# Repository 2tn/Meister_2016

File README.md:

# Meister_2016
2016年度Meister鳥人間プロジェクトに搭載した飛行ロガー、「われのロガー3」のプログラム及び発注基板データ。

搭載したパーツは
- LPC11U35FHI33 (メインマイコン)
- MPU9250 (9軸センサー)
- MPL3115A2 (気圧センサー)
- NEO-7M (GPS)
- LTC4055 (LiPo充電制御チップ)
- TPS63001DRCT (3.3V DC/DCコンバーター)
- TWE-Lite (各搭載センサーとの通信用)

## われのロガー3
メインマイコンのプログラム。EMとFMのプロジェクトがあるが、FMのほうが最終的な完成版。
## 機速計
機速計のプログラム。よく覚えていない。
## 表示器 (7セグLED)
表示器のプログラム
## 表示器 (Android)
搭載したスマホ表示器のプログラム
## ダウンリンク
機体に積んであるスマホから、携帯回線経由で常時データをサーバーにアップロードしている。

このプログラムはそのデータを地上にいる観客がスマホで見るためのもの
## 基板
発注した基板データ、たくさんある…
- main_16

  われのロガー3の基板データ
- main_16_writer

  われのロガー3専用のデバッグ用機器、われのロガー3の下にはめてUSBでPCと接続することで、われのロガー3をデバッグできる。
  プログラムは、トラ技ARMライターのものをつかう。
- main_15

  2015年度の基板を回路図に落とし込んだもの  
- display

  表示器の回路設計図
- speedmeter

  機速計の回路設計図
- TWE-Lite_USB

  TWE LiteにUSB-UART変換チップをくっつけて、PCで使いやすくするための基板

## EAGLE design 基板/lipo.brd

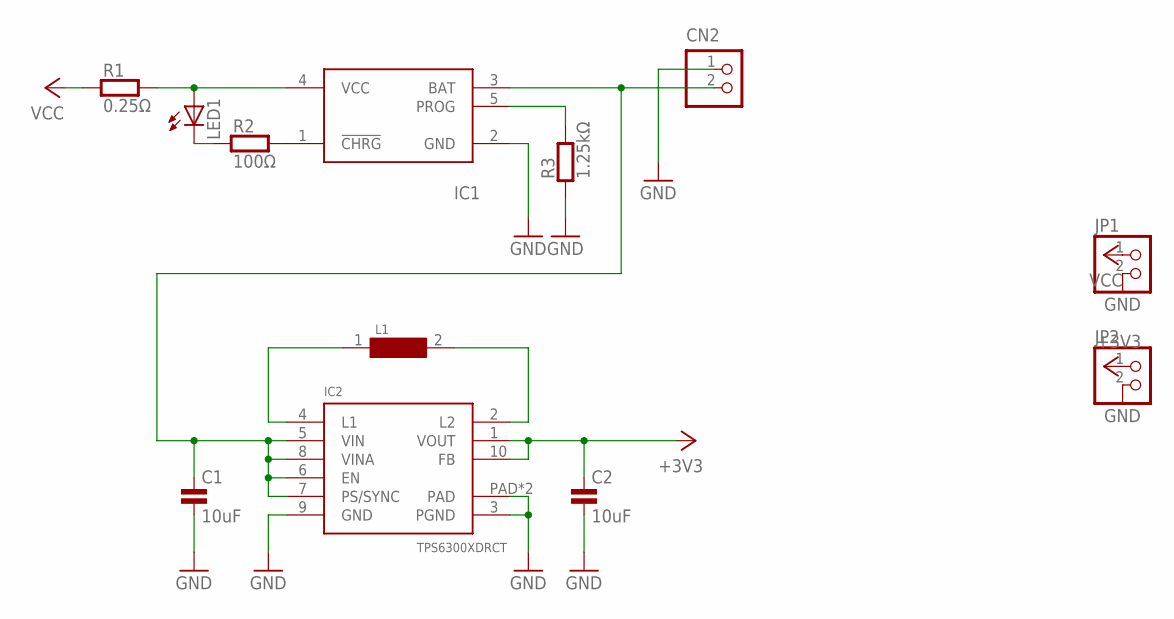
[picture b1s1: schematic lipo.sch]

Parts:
C1, C2: 10uF; 0603
CN2: S2B-PH-K-S
IC1: LTC4054; TSOT23-5
IC2: TPS6300XDRCT; S-PVSON-N10
JP1, JP2: PINHD-1X2; 1X02
L1: VLF4012ST
LED1: LEDSML0603; SML0603
R1: 0.25Ω; 0603
R2: 100Ω; 0603
R3: 1.25kΩ; 0603

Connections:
+3V3: C2.1, IC2.1 (VOUT), IC2.10 (FB), JP2.1
GND: C1.2, C2.2, CN2.1, IC1.2 (GND), IC2.3 (PGND), IC2.9 (GND), IC2.PAD, IC2.PAD@1 (PAD), JP1.2, JP2.2, R3.1
unnamed: IC1.5 (PROG), R3.2
unnamed: IC1.4 (VCC), LED1.A, R1.2
unnamed: IC1.1 (!CHRG!), R2.2
unnamed: LED1.C, R2.1
unnamed: IC2.4 (L1), L1.1
unnamed: IC2.2 (L2), L1.2
unnamed: C1.1, CN2.2, IC1.3 (BAT), IC2.5 (VIN), IC2.6 (EN), IC2.7 (PS/SYNC), IC2.8 (VINA)
VCC: JP1.1, R1.1

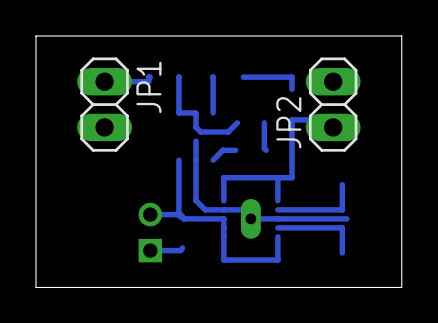
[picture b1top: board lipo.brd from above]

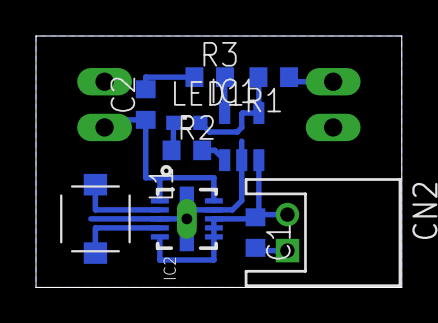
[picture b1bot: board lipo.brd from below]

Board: 2 copper layers, 20.3 x 14.0 mm, 12 parts (10 on the bottom side), 10 nets.

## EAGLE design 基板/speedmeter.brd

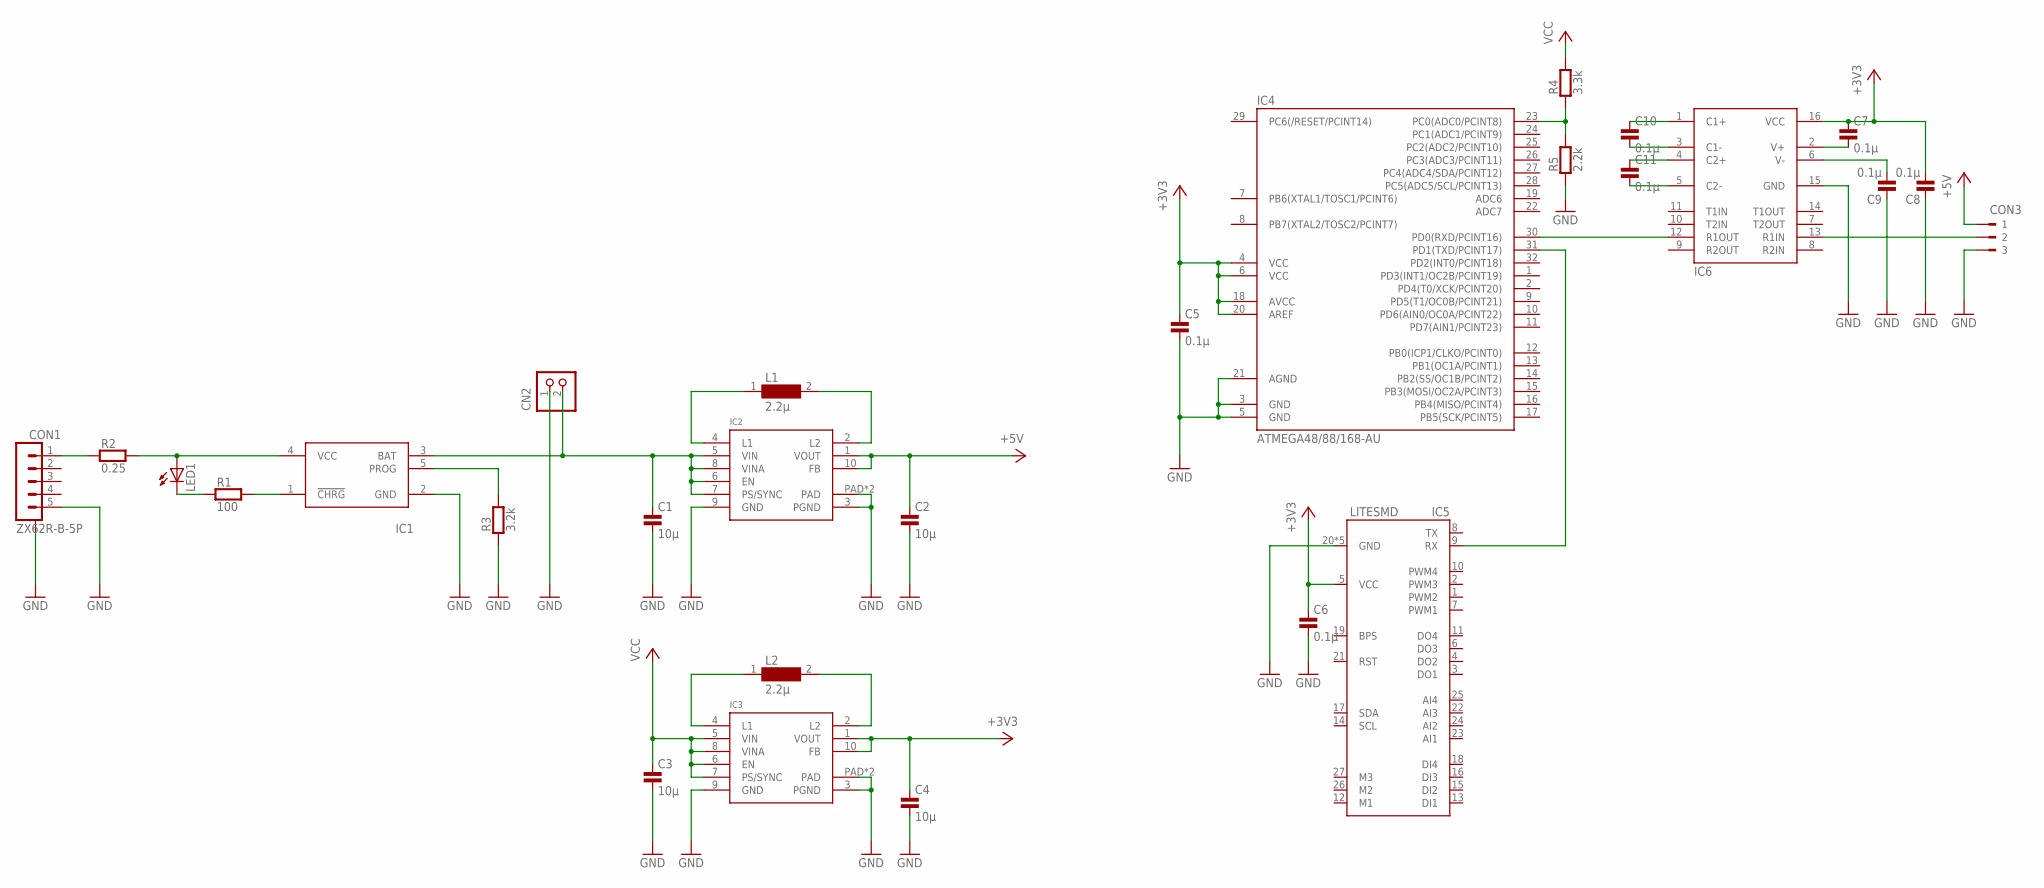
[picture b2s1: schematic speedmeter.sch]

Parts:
C1, C2, C3, C4: 10μ; 0603
C5, C6, C7, C8, C9, C10, C11: 0.1μ; 0603
CN2: S2B-PH-K-S
CON1: ZX62R-B-5P; MICRO-B
CON3: 180-3
IC1: LTC4054; TSOT23-5
IC2, IC3: TPS6300XDRCT; S-PVSON-N10
IC4: ATMEGA48/88/168-AU; TQFP32-08
IC5: LITESMD; LITE
IC6: ADM3202ARN; SOP16
L1, L2: 2.2μ; VLF4012ST
LED1: LEDSML0603; SML0603
R1: 100; 0603
R2: 0.25; 0603
R3: 3.2k; 0603
R4: 3.3k; 0603
R5: 2.2k; 0603

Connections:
+3V3: C4.1, C5.1, C6.1, C7.1, C8.2, IC3.1 (VOUT), IC3.10 (FB), IC4.4 (VCC), IC4.6 (VCC), IC4.18 (AVCC), IC4.20 (AREF), IC5.5 (VCC), IC6.16 (VCC)
+5V: C2.1, CON3.1, IC2.1 (VOUT), IC2.10 (FB)
GND: C1.2, C2.2, C3.2, C4.2, C5.2, C6.2, C8.1, C9.1, CN2.1, CON1.5 (1.VBUS), CON1.CASE@1, CON1.CASE@2, CON1.CASE@3, CON1.CASE@4, CON3.3, IC1.2 (GND), IC2.3 (PGND), IC2.9 (GND), IC2.PAD, IC2.PAD@1 (PAD), IC3.3 (PGND), IC3.9 (GND), IC3.PAD, IC3.PAD@1 (PAD), IC4.3 (GND), IC4.5 (GND), IC4.21 (AGND), IC5.20 (GND), IC5.28 (GND), IC5.30 (GND), IC5.31 (GND), IC5.32 (GND), IC6.15 (GND), R3.1, R5.1
unnamed: CON1.1 (5.GND), R2.1
unnamed: IC1.4 (VCC), LED1.A, R2.2
unnamed: LED1.C, R1.1
unnamed: IC1.1 (!CHRG!), R1.2
unnamed: IC1.5 (PROG), R3.2
unnamed: IC2.4 (L1), L1.1
unnamed: IC2.2 (L2), L1.2
unnamed: CON3.2, IC6.13 (R1IN)
unnamed: IC3.4 (L1), L2.1
unnamed: IC3.2 (L2), L2.2
unnamed: IC4.23 (PC0(ADC0/PCINT8)), R4.1, R5.2
unnamed: IC4.31 (PD1(TXD/PCINT17)), IC5.9 (RX)
unnamed: C7.2, IC6.2 (V+)
unnamed: C9.2, IC6.6 (V-)
unnamed: C10.1, IC6.1 (C1+)
unnamed: C10.2, IC6.3 (C1-)
unnamed: C11.1, IC6.4 (C2+)
unnamed: C11.2, IC6.5 (C2-)
unnamed: IC4.30 (PD0(RXD/PCINT16)), IC6.12 (R1OUT)
VCC: C1.1, C3.1, CN2.2, IC1.3 (BAT), IC2.5 (VIN), IC2.6 (EN), IC2.7 (PS/SYNC), IC2.8 (VINA), IC3.5 (VIN), IC3.6 (EN), IC3.7 (PS/SYNC), IC3.8 (VINA), R4.2

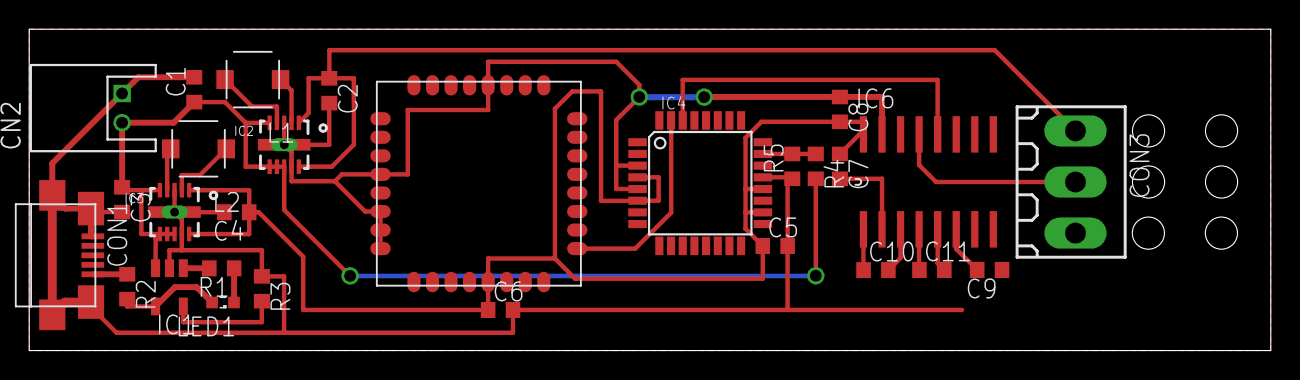
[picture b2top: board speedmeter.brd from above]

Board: 2 copper layers, 85.0 x 22.0 mm, 28 parts (0 on the bottom side), 23 nets.

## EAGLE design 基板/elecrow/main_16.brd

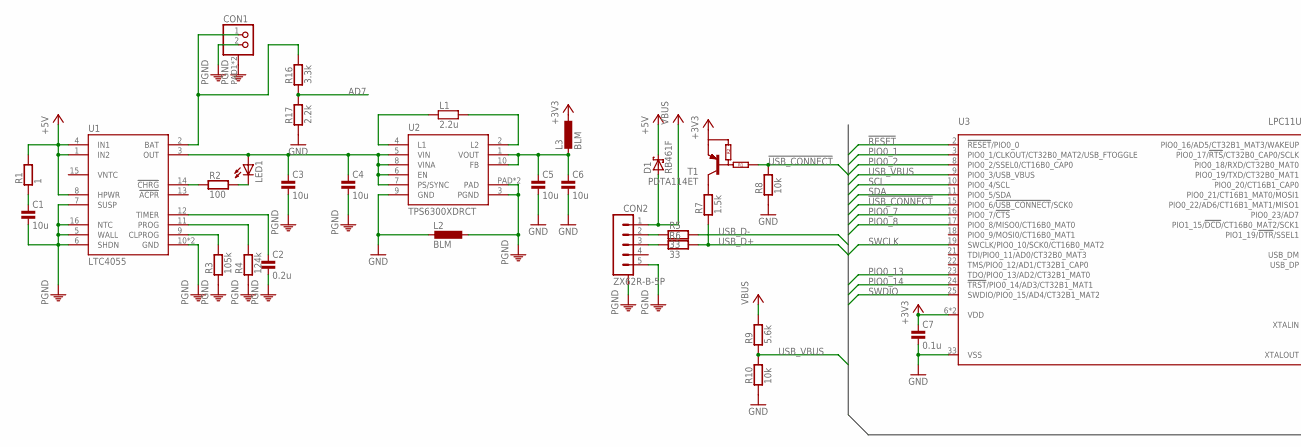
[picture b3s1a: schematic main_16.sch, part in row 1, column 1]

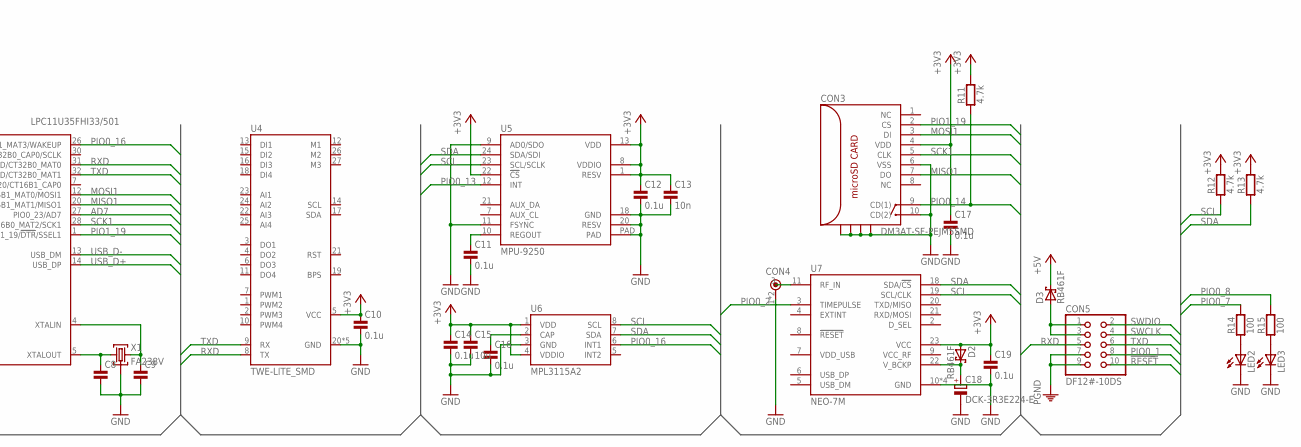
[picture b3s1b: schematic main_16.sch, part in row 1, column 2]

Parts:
C1, C3, C4, C5, C6: 10u; 0603
C2: 0.2u; 0402
C7, C10, C11, C12, C14, C16, C17, C19: 0.1u; 0402
C8, C9: C0402; 0402
C13: 10n; 0402
C15: 10u; 0402
C18: DCK-3R3E224-E
CON1: JST-PH2
CON2: ZX62R-B-5P; MICRO-B
CON3: DM3AT-SF-PEJM5SMD; DM3AT-SF-PEJM5
CON4: U.FL; U.FL-R-SMT-1
CON5: DF12#-10DS; DF12A-10DS
D1, D2, D3: RB461F; UMD3
L1: 2.2u; VLF4012ST
L2, L3: BLM; C0603K
LED1, LED2, LED3: LEDSML0603; SML0603
R1: 1; 0402
R2, R14, R15: 100; 0402
R3: 105k; 0402
R4: 124k; 0402
R5, R6: 33; 0402
R7: 1.5k; 0402
R8, R10: 10k; 0402
R9: 5.6k; 0402
R11, R12, R13: 4.7k; 0402
R16: 3.3k; 0402
R17: 2.2k; 0402
T1: PDTA114ET; SOT23
U1: LTC4055; QFN16
U2: TPS6300XDRCT; S-PVSON-N10
U3: LPC11U35FHI33/501; SOT617-3
U4: TWE-LITE_SMD; LITE
U5: MPU-9250
U6: MPL3115A2
U7: NEO-7M
X1: FA238V; V66RA

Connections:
!RESET!: CON5.10, U3.2 (!RESET!/PIO0_0)
!USB_CONNECT!: R8.2, T1.1 (INPUT), U3.15 (PIO0_6/!USB_CONNECT!/SCK0)
+3V3: C7.1, C10.1, C12.1, C13.1, C14.1, C15.1, C17.1, C19.1, CON3.4 (VDD), D2.2 (A), L3.1, R11.2, R12.2, R13.2, T1.2 (E), U3.6 (VDD), U3.29 (VDD), U4.5 (VCC), U5.1 (RESV), U5.8 (VDDIO), U5.13 (VDD), U5.22 (!CS!), U6.1 (VDD), U6.4 (VDDIO), U7.23 (VCC)
+5V: D1.3 (C), D3.3 (C), R1.2, U1.1 (IN2), U1.4 (IN1), U1.8 (HPWR)
AD7: R16.1, R17.2, U3.27 (PIO0_23/AD7)
GND: C5.2, C6.2, C7.2, C8.2, C9.2, C10.2, C11.2, C12.2, C13.2, C14.2, C15.2, C16.2, C17.2, C18.1 (-), C19.2, CON3.6 (VSS), CON3.10 (CD(2)), CON3.P$10, CON3.P$11, CON3.P$12, CON3.P$14, CON4.1 (GND), CON4.2 (GND), L2.2, LED2.C, LED3.C, R8.1, R10.1, R17.1, U2.9 (GND), U3.33 (VSS), U4.20 (GND), U4.28 (GND), U4.30 (GND), U4.31 (GND), U4.32 (GND), U5.9 (AD0/SDO), U5.11 (FSYNC), U5.18 (GND), U5.20 (RESV), U5.PAD, U6.3 (GND), U7.10 (GND), U7.12 (GND), U7.13 (GND), U7.24 (GND), X1.P2GND (GND), X1.P4GND (GND)
MISO1: CON3.7 (DO), U3.20 (PIO0_22/AD6/CT16B1_MAT1/MISO1)
MOSI1: CON3.3 (DI), U3.12 (PIO0_21/CT16B1_MAT0/MOSI1)
unnamed: C8.1, U3.5 (XTALOUT), X1.P1X1 (X1)
unnamed: CON2.2 (2.D-), R5.1
unnamed: C9.1, U3.4 (XTALIN), X1.P3X2 (X2)
unnamed: CON2.3 (3.D+), R6.1
unnamed: R7.2, T1.3 (C)
unnamed: LED3.A, R15.1
unnamed: CON4.3 (RF), U7.11 (RF_IN)
unnamed: C16.1, U6.2 (CAP)
unnamed: L1.2, U2.2 (L2)
unnamed: C11.1, U5.10 (REGOUT)
unnamed: L1.1, U2.4 (L1)
unnamed: LED2.A, R14.1
unnamed: C1.1, R1.1
unnamed: C5.1, C6.1, L3.2, U2.1 (VOUT), U2.10 (FB)
unnamed: CON5.1, CON5.3, D3.2 (A)
unnamed: R3.2, U1.9 (CLPROG)
unnamed: R4.2, U1.11 (PROG)
unnamed: C2.1, U1.12 (TIMER)
unnamed: R2.1, U1.14 (!CHRG!)
unnamed: LED1.C, R2.2
unnamed: C3.1, C4.1, LED1.A, U1.3 (OUT), U2.5 (VIN), U2.6 (EN), U2.7 (PS/SYNC), U2.8 (VINA)
unnamed: CON1.1, R16.2, U1.2 (BAT)
unnamed: C18.2 (+), D2.3 (C), U7.22 (V_BCKP)
PGND: C1.2, C2.2, C3.2, C4.2, CON1.2, CON1.PAD1, CON1.PAD2, CON2.5 (5.GND), CON2.CASE@1, CON2.CASE@2, CON2.CASE@3, CON2.CASE@4, CON5.7, CON5.9, L2.1, R3.1, R4.1, U1.5 (WALL), U1.6 (SHDN), U1.7 (SUSP), U1.10 (GND), U1.16 (NTC), U1.PAD (GND), U2.3 (PGND), U2.PAD, U2.PAD@1 (PAD)
PIO0_1: CON5.8, U3.3 (PIO0_1/CLKOUT/CT32B0_MAT2/USB_FTOGGLE)
PIO0_2: U3.8 (PIO0_2/SSEL0/CT16B0_CAP0), U7.3 (TIMEPULSE)
PIO0_7: R14.2, U3.16 (PIO0_7/!CTS!)
PIO0_8: R15.2, U3.17 (PIO0_8/MISO0/CT16B0_MAT0)
PIO0_13: U3.23 (TDO/PIO0_13/AD2/CT32B1_MAT0), U5.12 (INT)
PIO0_14: CON3.9 (CD(1)), R11.1, U3.24 (!TRST!/PIO0_14/AD3/CT32B1_MAT1)
PIO0_16: U3.26 (PIO0_16/AD5/CT32B1_MAT3/WAKEUP), U6.6 (INT1)
PIO1_19: CON3.2 (CS), U3.1 (PIO1_19/!DTR!/SSEL1)
RXD: CON5.5, U3.31 (PIO0_18/RXD/CT32B0_MAT0), U4.8 (TX)
SCK1: CON3.5 (CLK), U3.28 (PIO1_15/!DCD!/CT16B0_MAT2/SCK1)
SCL: R12.1, U3.10 (PIO0_4/SCL), U5.23 (SCL/SCLK), U6.8 (SCL), U7.19 (SCL/CLK)
SDA: R13.1, U3.11 (PIO0_5/SDA), U5.24 (SDA/SDI), U6.7 (SDA), U7.18 (SDA/!CS!)
SWCLK: CON5.4, U3.19 (SWCLK/PIO0_10/SCK0/CT16B0_MAT2)
SWDIO: CON5.2, U3.25 (SWDIO/PIO0_15/AD4/CT32B1_MAT2)
TXD: CON5.6, U3.32 (PIO0_19/TXD/CT32B0_MAT1), U4.9 (RX)
USB_D+: R6.2, R7.1, U3.14 (USB_DP)
USB_D-: R5.2, U3.13 (USB_DM)
USB_VBUS: R9.1, R10.2, U3.9 (PIO0_3/USB_VBUS)
VBUS: CON2.1 (1.VBUS), D1.2 (A), R9.2
VDD_USB: U7.7 (VDD_USB)
VNTC: U1.15 (VNTC)

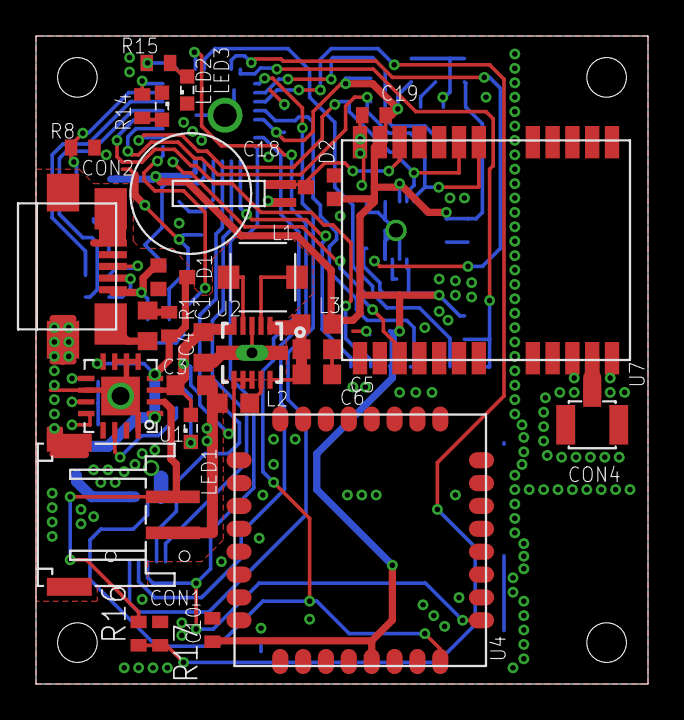
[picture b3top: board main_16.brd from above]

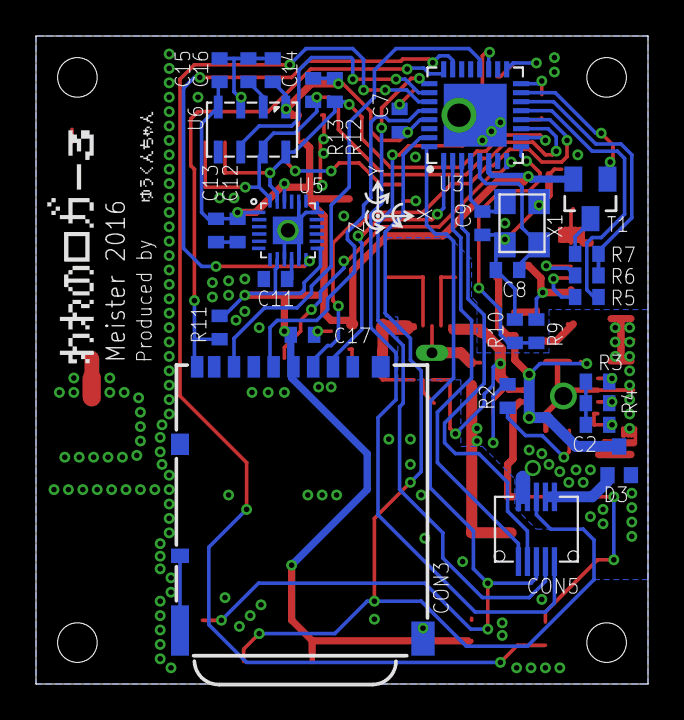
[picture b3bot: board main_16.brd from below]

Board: 2 copper layers, 34.0 x 36.0 mm, 60 parts (31 on the bottom side), 51 nets.

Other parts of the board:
U$1: DIRECTION

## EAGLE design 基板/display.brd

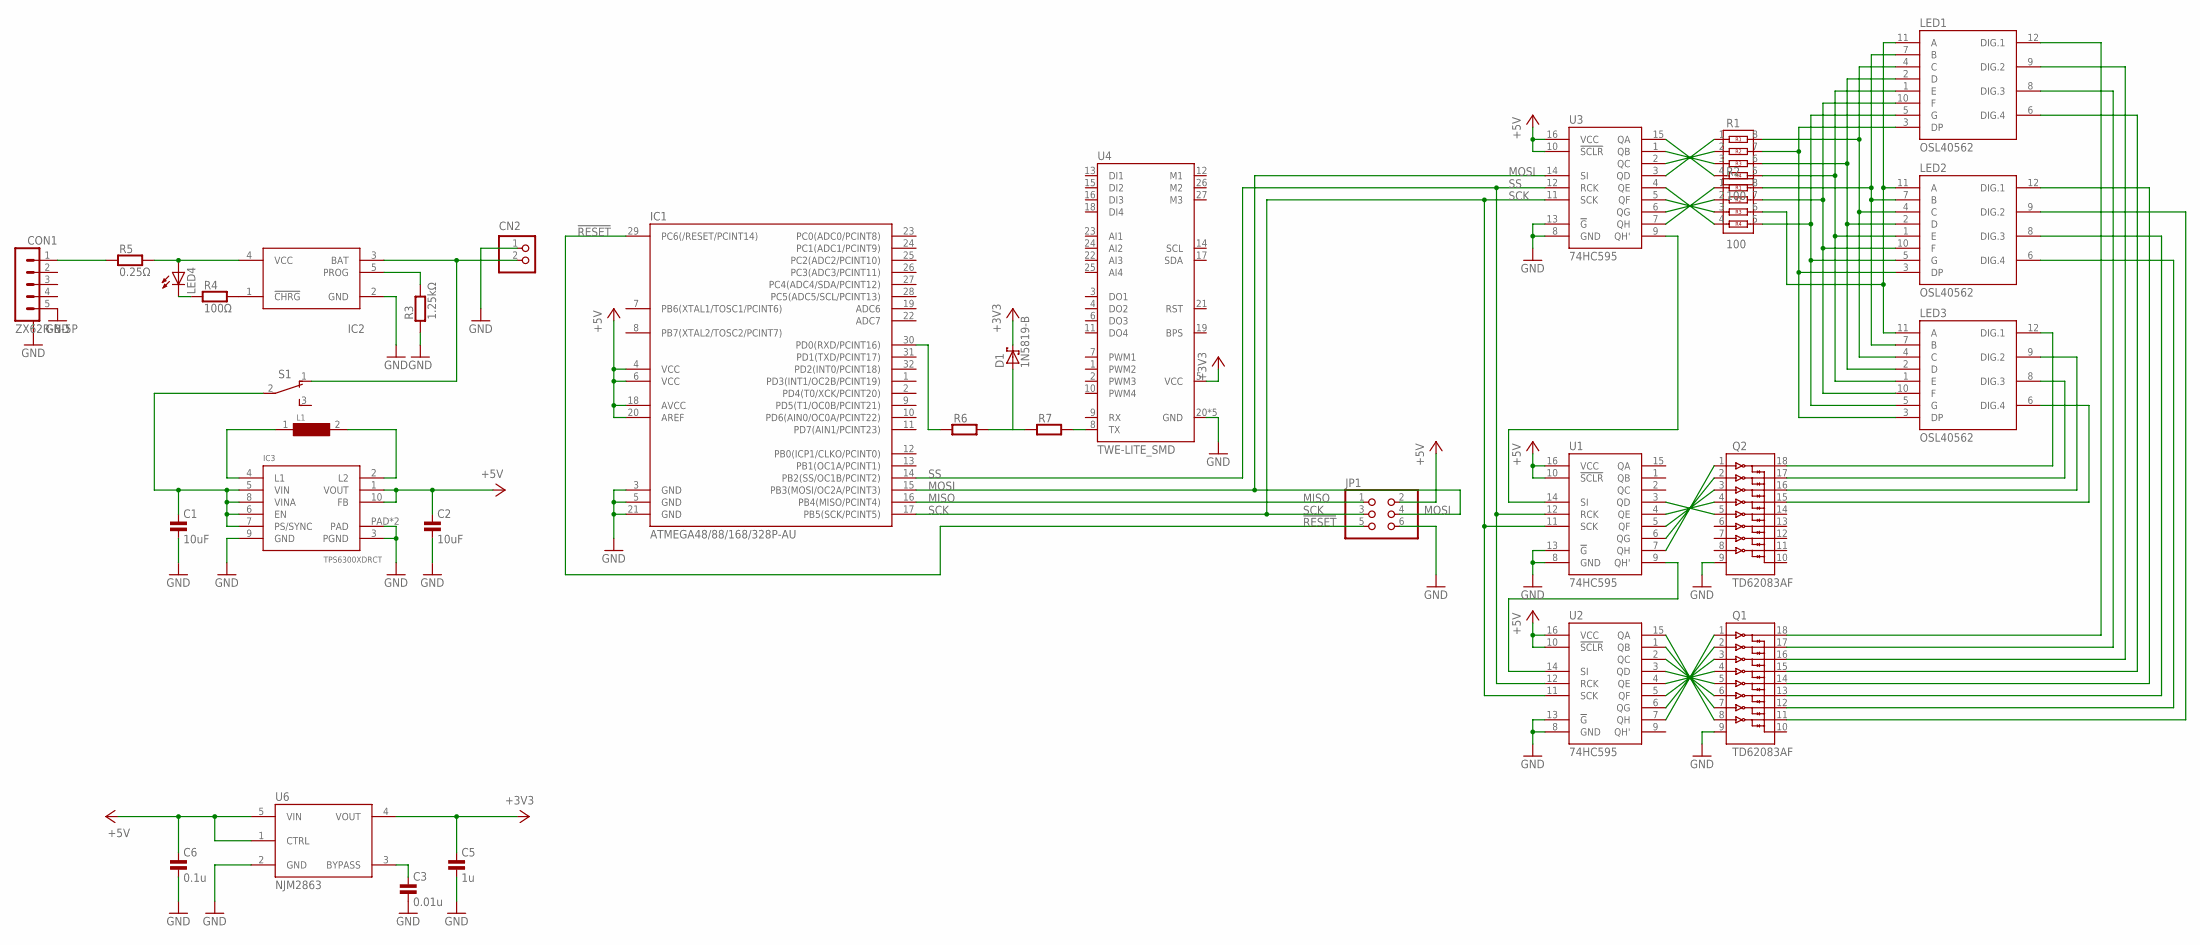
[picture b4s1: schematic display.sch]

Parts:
C1, C2: 10uF; 0603@1
C3: 0.01u; 0603@1
C5: 1u; 0603@1
C6: 0.1u; 0603@1
CN2: S2B-PH-K-S
CON1: ZX62R-B-5P; MICRO-B
D1: 1N5819-B; DO41-7.6
IC1: ATMEGA48/88/168/328P-AU; TQFP32
IC2: LTC4054; TSOT23-5
IC3: TPS6300XDRCT; S-PVSON-N10
JP1: PINHD-2X3; 2X03
L1: VLF4012ST
LED1, LED2, LED3: OSL40562; 7SEG_4DIG
LED4: LEDSML0603; SML0603
Q1, Q2: TD62083AF; SOP18
R1, R2: 100; BCN164AB
R3: 1.25kΩ; 0603
R4: 100Ω; 0603
R5: 0.25Ω; 0603
R6, R7: R0204/5; 0204/5
S1: SS-12D00
U1, U2, U3: 74HC595; SOP16
U4: TWE-LITE_SMD; LITE
U6: NJM2863; SOT23_5PIN

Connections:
!RESET!: IC1.29 (PC6(/RESET/PCINT14)), JP1.5
+3V2: C1.1, IC3.5 (VIN), IC3.6 (EN), IC3.7 (PS/SYNC), IC3.8 (VINA), S1.2
+3V3: C5.1, D1.C, U4.5 (VCC), U6.4 (VOUT)
+5V: C2.1, C6.1, IC1.4 (VCC), IC1.6 (VCC), IC1.18 (AVCC), IC1.20 (AREF), IC3.1 (VOUT), IC3.10 (FB), JP1.2, U1.10 (!SCLR!), U1.16 (VCC), U2.10 (!SCLR!), U2.16 (VCC), U3.10 (!SCLR!), U3.16 (VCC), U6.1 (CTRL), U6.5 (VIN)
GND: C1.2, C2.2, C3.2, C5.2, C6.2, CN2.1, CON1.5 (5.GND), CON1.CASE@1, CON1.CASE@2, CON1.CASE@3, CON1.CASE@4, IC1.3 (GND), IC1.5 (GND), IC1.21 (GND), IC2.2 (GND), IC3.3 (PGND), IC3.9 (GND), IC3.PAD, IC3.PAD@1 (PAD), JP1.6, Q1.9 (GND), Q2.9 (GND), R3.1, U1.8 (GND), U1.13 (!G!), U2.8 (GND), U2.13 (!G!), U3.8 (GND), U3.13 (!G!), U4.20 (GND), U4.28 (GND), U4.30 (GND), U4.31 (GND), U4.32 (GND), U6.2 (GND)
MISO: IC1.16 (PB4(MISO/PCINT4)), JP1.1
MOSI: IC1.15 (PB3(MOSI/OC2A/PCINT3)), JP1.4, U3.14 (SI)
unnamed: LED1.11 (A), LED2.11 (A), LED3.11 (A), R2.6
unnamed: LED1.7 (B), LED2.7 (B), LED3.7 (B), R2.8
unnamed: LED1.4 (C), LED2.4 (C), LED3.4 (C), R1.8
unnamed: LED1.2 (D), LED2.2 (D), LED3.2 (D), R1.6
unnamed: LED1.1 (E), LED2.1 (E), LED3.1 (E), R1.5
unnamed: LED1.10 (F), LED2.10 (F), LED3.10 (F), R2.7
unnamed: LED1.5 (G), LED2.5 (G), LED3.5 (G), R2.5
unnamed: LED1.3 (DP), LED2.3 (DP), LED3.3 (DP), R1.7
unnamed: CN2.2, IC2.3 (BAT), S1.1 (O)
unnamed: C3.1, U6.3 (BYPASS)
unnamed: Q2.5 (I5), U1.3 (QD)
unnamed: Q2.4 (I4), U1.4 (QE)
unnamed: Q2.3 (I3), U1.5 (QF)
unnamed: Q2.2 (I2), U1.6 (QG)
unnamed: Q2.1 (I1), U1.7 (QH)
unnamed: LED2.9 (DIG.2), Q1.11 (O8)
unnamed: LED2.8 (DIG.3), Q1.13 (O6)
unnamed: LED2.6 (DIG.4), Q1.12 (O7)
unnamed: LED2.12 (DIG.1), Q1.14 (O5)
unnamed: LED1.6 (DIG.4), Q1.15 (O4)
unnamed: LED1.12 (DIG.1), Q1.18 (O1)
unnamed: LED1.8 (DIG.3), Q1.17 (O2)
unnamed: LED1.9 (DIG.2), Q1.16 (O3)
unnamed: LED3.12 (DIG.1), Q2.18 (O1)
unnamed: LED3.9 (DIG.2), Q2.16 (O3)
unnamed: LED3.8 (DIG.3), Q2.17 (O2)
unnamed: LED3.6 (DIG.4), Q2.15 (O4)
unnamed: Q1.8 (I8), U2.15 (QA)
unnamed: Q1.7 (I7), U2.1 (QB)
unnamed: Q1.6 (I6), U2.2 (QC)
unnamed: Q1.5 (I5), U2.3 (QD)
unnamed: Q1.4 (I4), U2.4 (QE)
unnamed: Q1.3 (I3), U2.5 (QF)
unnamed: Q1.2 (I2), U2.6 (QG)
unnamed: Q1.1 (I1), U2.7 (QH)
unnamed: U1.9 (QH'), U2.14 (SI)
unnamed: R1.4, U3.15 (QA)
unnamed: R1.3, U3.1 (QB)
unnamed: R1.2, U3.2 (QC)
unnamed: R1.1, U3.3 (QD)
unnamed: R2.4, U3.4 (QE)
unnamed: R2.3, U3.5 (QF)
unnamed: R2.2, U3.6 (QG)
unnamed: R2.1, U3.7 (QH)
unnamed: U1.14 (SI), U3.9 (QH')
unnamed: IC1.30 (PD0(RXD/PCINT16)), R6.1
unnamed: IC2.5 (PROG), R3.2
unnamed: IC2.4 (VCC), LED4.A, R5.2
unnamed: IC2.1 (!CHRG!), R4.2
unnamed: LED4.C, R4.1
unnamed: IC3.4 (L1), L1.1
unnamed: IC3.2 (L2), L1.2
unnamed: D1.A, R6.2, R7.1
unnamed: R7.2, U4.8 (TX)
unnamed: CON1.1 (1.VBUS), R5.1
SCK: IC1.17 (PB5(SCK/PCINT5)), JP1.3, U1.11 (SCK), U2.11 (SCK), U3.11 (SCK)
SS: IC1.14 (PB2(SS/OC1B/PCINT2)), U1.12 (RCK), U2.12 (RCK), U3.12 (RCK)

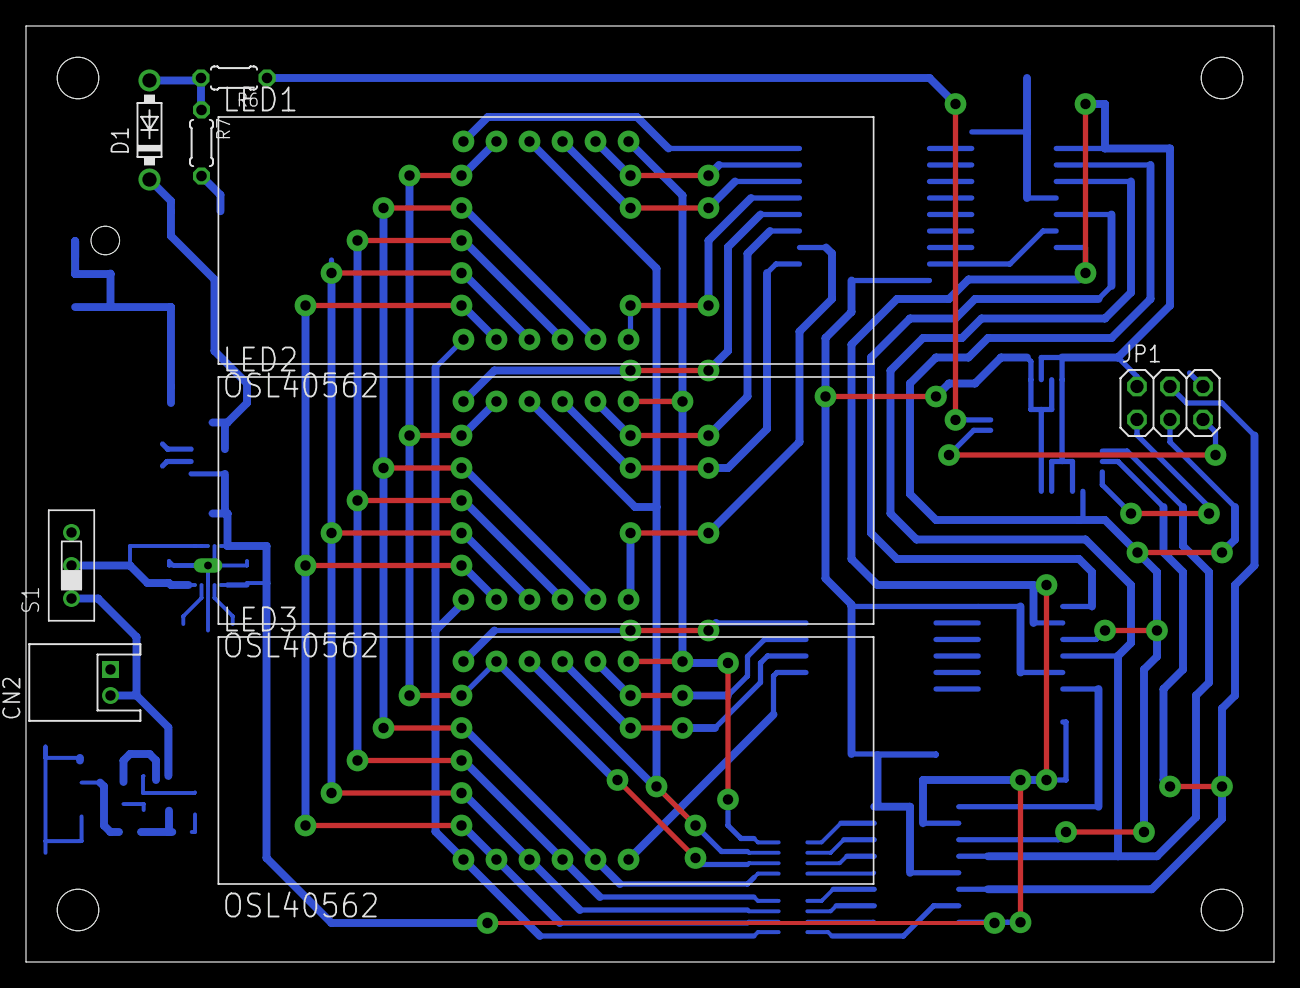
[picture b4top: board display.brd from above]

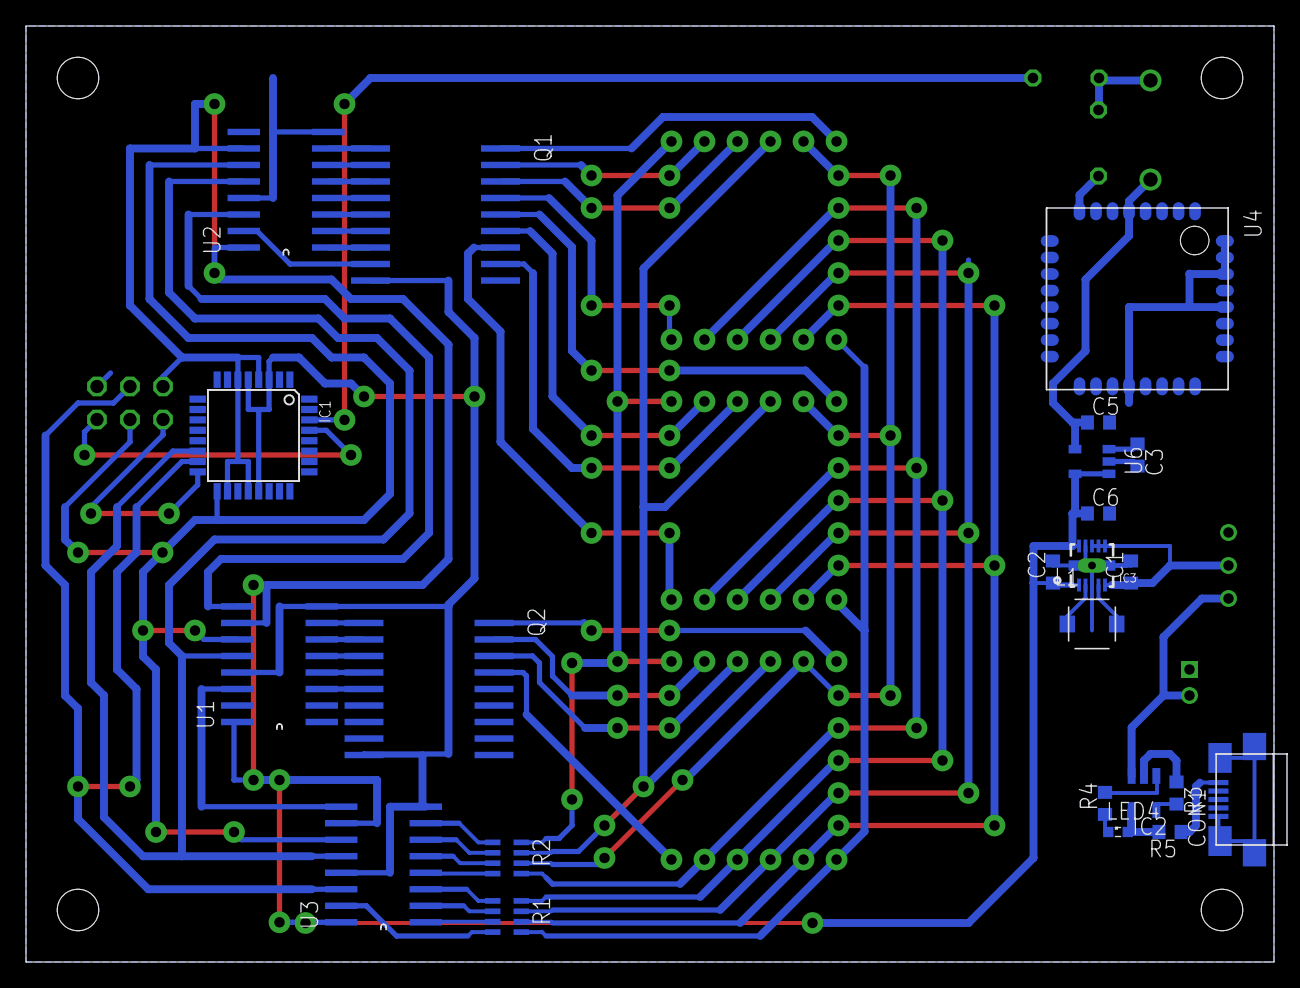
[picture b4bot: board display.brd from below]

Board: 2 copper layers, 96.0 x 72.0 mm, 32 parts (23 on the bottom side), 64 nets.

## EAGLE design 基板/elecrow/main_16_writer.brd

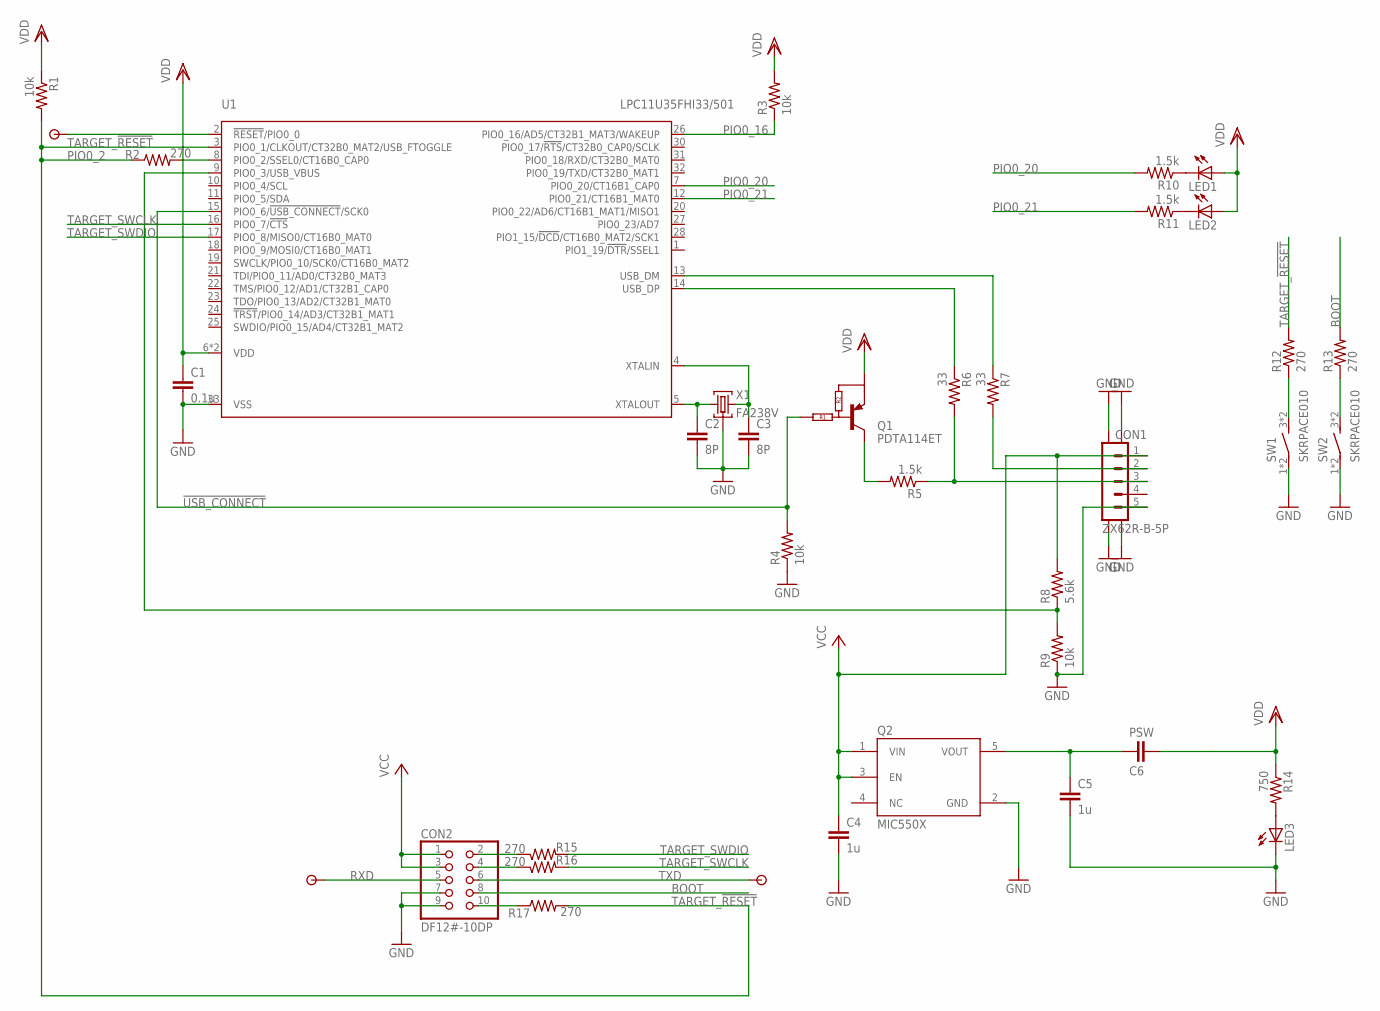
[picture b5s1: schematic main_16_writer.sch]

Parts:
C1: 0.1u; C0402
C2, C3: 8P; C0402
C4, C5: 1u; C0402
C6: PSW; C3225
CON1: ZX62R-B-5P; MICRO-B
CON2: DF12#-10DP; DF12D-10DP
LED1, LED2, LED3: LEDSML0603; SML0603
Q1: PDTA114ET; SOT23
Q2: MIC550X; SOT23_5PIN
R1, R3, R4, R9: 10k; R0402
R2, R12, R13, R15, R16, R17: 270; R0402
R5, R10, R11: 1.5k; R0402
R6, R7: 33; R0402
R8: 5.6k; R0402
R14: 750; R0402
SW1, SW2: SKRPACE010
U1: LPC11U35FHI33/501; SOT617-3
U$1, U$2, U$3: TESTPAD
X1: FA238V; V66RA

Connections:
!USB_CONNECT!: Q1.1 (INPUT), R4.2, U1.15 (PIO0_6/!USB_CONNECT!/SCK0)
BOOT: CON2.8, R13.2
D+USB: CON1.3 (3.D+), R5.1, R6.2
D-USB: CON1.2 (4.ID), R7.2
GND: C1.2, C2.2, C3.2, C4.2, C5.2, CON1.5 (1.VBUS), CON1.CASE@1 (1), CON1.CASE@2 (2), CON1.CASE@3 (3), CON1.CASE@4 (4), CON2.7, CON2.9, LED3.C, Q2.2 (GND), R4.1, R9.1, SW1.1, SW1.2, SW2.1, SW2.2, U1.33 (VSS), X1.P2GND (GND), X1.P4GND (GND)
unnamed: LED1.C, R10.1
unnamed: C2.1, U1.5 (XTALOUT), X1.P1X1 (X1)
unnamed: C3.1, U1.4 (XTALIN), X1.P3X2 (X2)
unnamed: C5.1, C6.2, Q2.5 (VOUT)
unnamed: R12.1, SW1.3 (S), SW1.4 (S)
unnamed: Q1.3 (C), R5.2
unnamed: R6.1, U1.14 (USB_DP)
unnamed: R7.1, U1.13 (USB_DM)
unnamed: CON2.10, R17.1
unnamed: LED2.C, R11.1
unnamed: R13.1, SW2.3 (S), SW2.4 (S)
unnamed: U1.2 (!RESET!/PIO0_0), U$3.P$1
unnamed: CON2.2, R15.1
unnamed: CON2.4, R16.1
unnamed: LED3.A, R14.2
PIO0_2: R2.2, U1.8 (PIO0_2/SSEL0/CT16B0_CAP0)
PIO0_16: R3.1, U1.26 (PIO0_16/AD5/CT32B1_MAT3/WAKEUP)
PIO0_20: R10.2, U1.7 (PIO0_20/CT16B1_CAP0)
PIO0_21: R11.2, U1.12 (PIO0_21/CT16B1_MAT0)
RXD: CON2.5, U$2.P$1
TARGET_!RESET!: R1.2, R2.1, R12.2, R17.2, U1.3 (PIO0_1/CLKOUT/CT32B0_MAT2/USB_FTOGGLE)
TARGET_SWCLK: R16.2, U1.16 (PIO0_7/!CTS!)
TARGET_SWDIO: R15.2, U1.17 (PIO0_8/MISO0/CT16B0_MAT0)
TXD: CON2.6, U$1.P$1
USB_VBUS: R8.1, R9.2, U1.9 (PIO0_3/USB_VBUS)
VCC: C4.1, CON1.1 (5.GND), CON2.1, CON2.3, Q2.1 (VIN), Q2.3 (EN), R8.2
VDD: C1.1, C6.1, LED1.A, LED2.A, Q1.2 (E), R1.1, R3.2, R14.1, U1.6 (VDD), U1.29 (VDD)

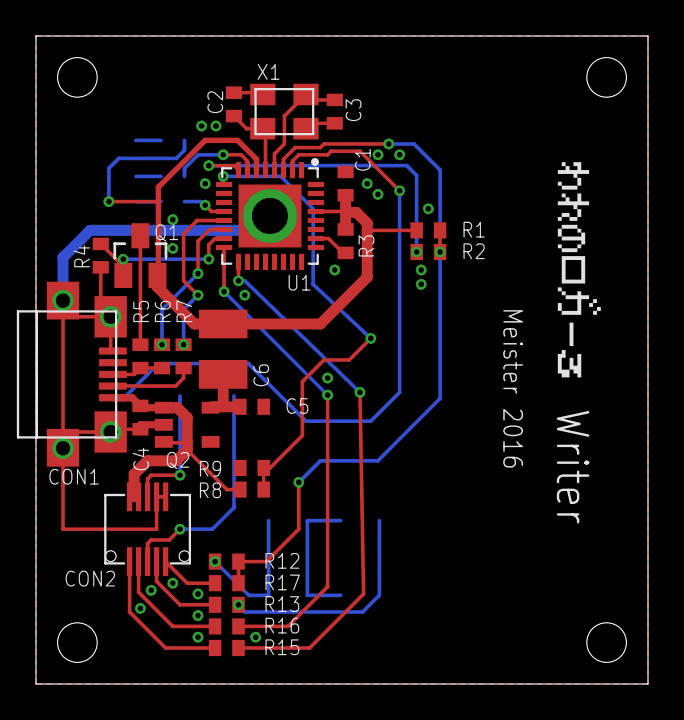
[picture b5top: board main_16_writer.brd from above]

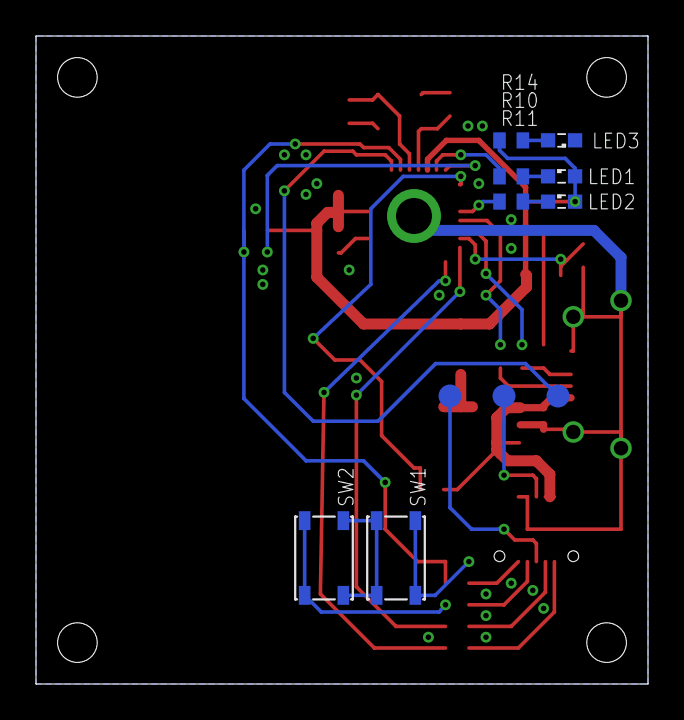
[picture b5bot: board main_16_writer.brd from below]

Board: 2 copper layers, 34.0 x 36.0 mm, 37 parts (12 on the bottom side), 32 nets.

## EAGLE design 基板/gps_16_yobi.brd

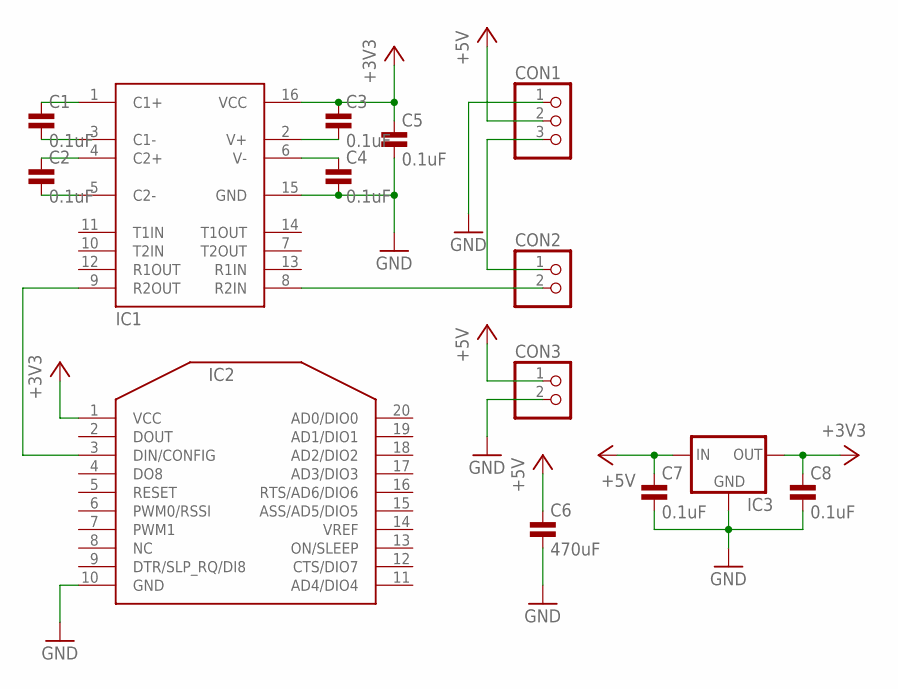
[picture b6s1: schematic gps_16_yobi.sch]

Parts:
C1, C2, C3, C4, C5, C7, C8: 0.1uF; 0603
C6: 470uF; C025-025X050
CON1: PINHD-1X3; 1X03
CON2, CON3: PINHD-1X2; 1X02
IC1: ADM3202ADM3202AN; IC16PIN
IC2: XBEE-PRO2MM; XBEE-ZB
IC3: 78MXXS

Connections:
+3V3: C3.1, C5.1, C8.1, IC1.16 (VCC), IC2.1 (VCC), IC3.OUT
+5V: C6.1, C7.1, CON1.2, CON3.1, IC3.IN
GND: C4.2, C5.2, C6.2, C7.2, C8.2, CON1.1, CON3.2, IC1.15 (GND), IC2.10 (GND), IC3.GND
GPS_OUT: CON1.3, CON2.1
unnamed: CON2.2, IC1.8 (R2IN)
unnamed: IC1.9 (R2OUT), IC2.3 (DIN/CONFIG)
unnamed: C2.1, IC1.4 (C2+)
unnamed: C2.2, IC1.5 (C2-)
unnamed: C1.1, IC1.1 (C1+)
unnamed: C1.2, IC1.3 (C1-)
unnamed: C4.1, IC1.6 (V-)
unnamed: C3.2, IC1.2 (V+)

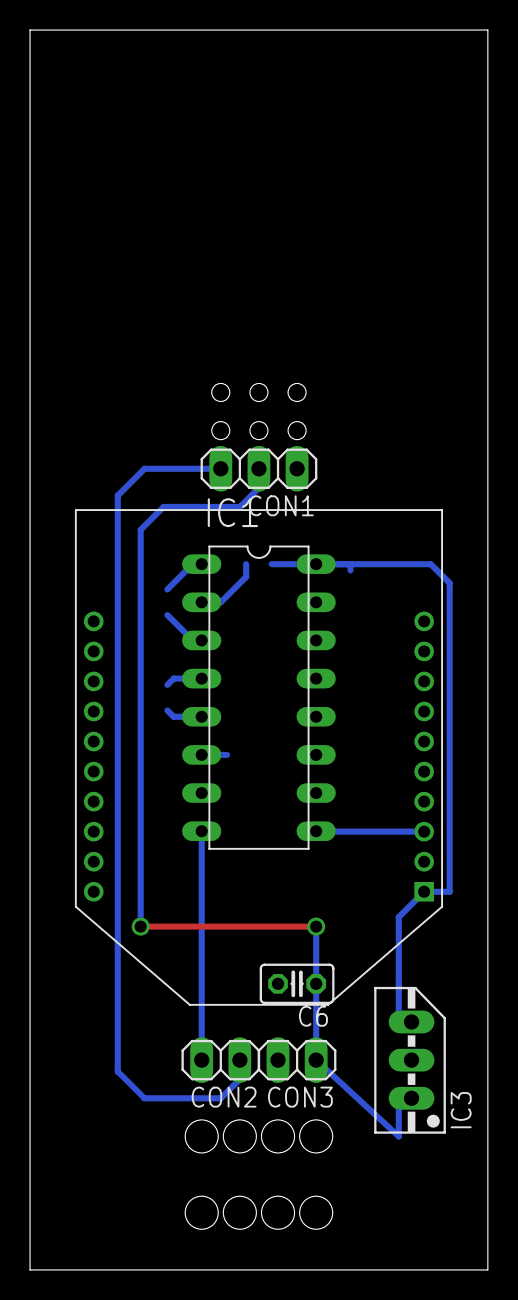
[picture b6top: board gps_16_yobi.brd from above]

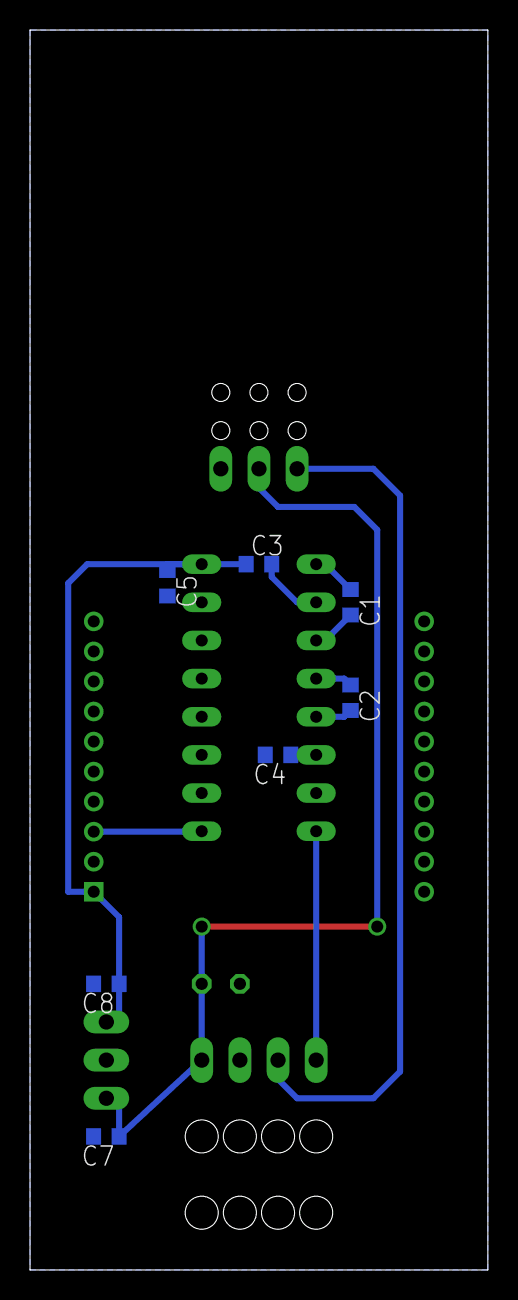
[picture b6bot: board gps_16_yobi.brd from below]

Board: 2 copper layers, 30.5 x 82.5 mm, 14 parts (7 on the bottom side), 12 nets.
